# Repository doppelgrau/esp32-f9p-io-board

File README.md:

# ESP32 F9P IO board

This PCB is a versatile IO plattform that provides computing power (ESP32) and IO interfaces to build GPS/RTK applications.

## Hardware Overview

- Power supply: 
    - Input 9V-28V (labeld 12V on the board), external connection on J4. 
    - Protected against wrong polarity (Diode D7 parallel to the relay K1)
    - Reduced inrush current (resistors R15/16 in serie with the starting diode D7 before the relay K1 closes and shortens the path).
    - V78E05-1000 (step down converter) PS1 generates 5V
    - AZ1117-3.3 LDO U2 generates 3V from the 5V supply.
    - 12A (slow) fuse soldered on the board. Recommended to use a 10A external fuse.
- ESP32-WROOM-32 U1 for computing-power, wifi, Bluetooth
- Arduino headers for the simpleRTK2B-F9P (uart 1 of the F9P connected)
- Serial interfaces
    - one uart (IO13/14) on the Arduino headers for the F9P
    - one uart (IO0/2) next to the arduino headers on two pins (J2) for the new simpleRTK2Blight. Since the two pins have a special meaning during boot, pulling TX to GND during startup results in the ESP going into programming mode.
    - one uart (IO15/16) for RS232 on the D-Sub connector J16
    - one uart (IO1/3) on the USB-Uart converter (J14) - Also supports programming with "RTS/DTR"
- I2C (IO32/33)
    - I2C with 3.3V logic level (J8 pin header, J13,17 [qwiic](https://www.sparkfun.com/qwiic) connector)
    - I2C with 5V logic level (J7 pin header)
    - internal used adresses:
        - 0x1C - Magnetometer part of the LSM9DS1 (U12)
        - 0x43 - FXL6408 port extender (IC 1)
        - 0x48 - ADS1115 (U4)
        - 0x6A - Accelerometer part of the LSM9DS1 (U12)
- CAN bus
    - Tranceiver (U2) + ESP32 integrated controler (TX IO5, RX IO35)
    - Termination resistor and sending messages can/must both be enabled with a jumper on J12
    - external connection J18
- Ethernet:
    - internal MAC, connected to LAN8720A on IO17,18,19,21,22,23,25,26,27
        - IO17 Clock
        - IO18 MDIO
        - IO23 MDC
    - PHY-Reset controlled with FXL6408-GPI01
    - ETH-Address of the LAN8720: 0
- IMU: 9 Axis, LSM9DS1 (U12). Magnetometer needs iron correction to be usable.
- Outputs
    - One H-bridge/motordriver with two VNH7070AS (U3/5), (PWM IO4, FXL6408-GPIO6/7 direction). External connected on J4
    - One H-bridge/motordriver with one VNH7070AS (U9), (PWM IO12, FXL6408-GPI04/5 direction), external connected on J3
    - One Relay (K2) controlled on FXL6408-GPI03, external connected on J3
    - One status LED (D2) controlled on FXL6408-GPI02
- Inputs
    - Three 15V tolerant (analog) inputs IO34, SENSOR_VN/36, SENSOR_VP/39, external connected on J1
    - Three 5V tolerant (analog) inputs on the ADS1115, first two cann be used to measure differential. Number four is hardwired to VCC/5V. External connected on J5
    - One Button (e.g. for entering configuration mode), on FXL6408-GPI00
- Connectors:
    - J1 - 6 pin PTSM header. 15V tolerant inputs and 12V for easy cabeling if used as switch
    - J2 - 2 Pin Uart
    - J3 - 7 pin PTSM header. Outputs of second H-bridge, two times ground (for using as two half bridges) and the three pins for the relay (comm, no, nc)
    - J4 - 4 pin CCA header. Power input and output of the first motor driver/h-bridge
    - J5 - 5 pin PTSM header. Three ADS1115 inputs, 5V and GND for easy cabeling (e.g. linear potentiometer)
    - J7 - 4 pin header. I2C 5V logic level + GND and 5V
    - J8 - 4 pin header. I2C 3V3 logic level + GND and 3V3
    - J9, J10, J11 - 8 pin header. Socket for the simpleRTK2B F9P
    - J12 - 2x2 horizontal pin header. Used for jumpers to enable CAN termination and/or CAN TX
    - J13, J17 - qwiic connector. I2C 3V3
    - J14 - micro USB connector. Can power 5V and 3V3 part of the PCB. Electricaly not isolated! Used for programming the ESP32
    - J15 - RJ45 ethernet connector
    - J16 - D-Sub connector (male). RS232
    - J18 - 2 pin PTSM header. CAN bus

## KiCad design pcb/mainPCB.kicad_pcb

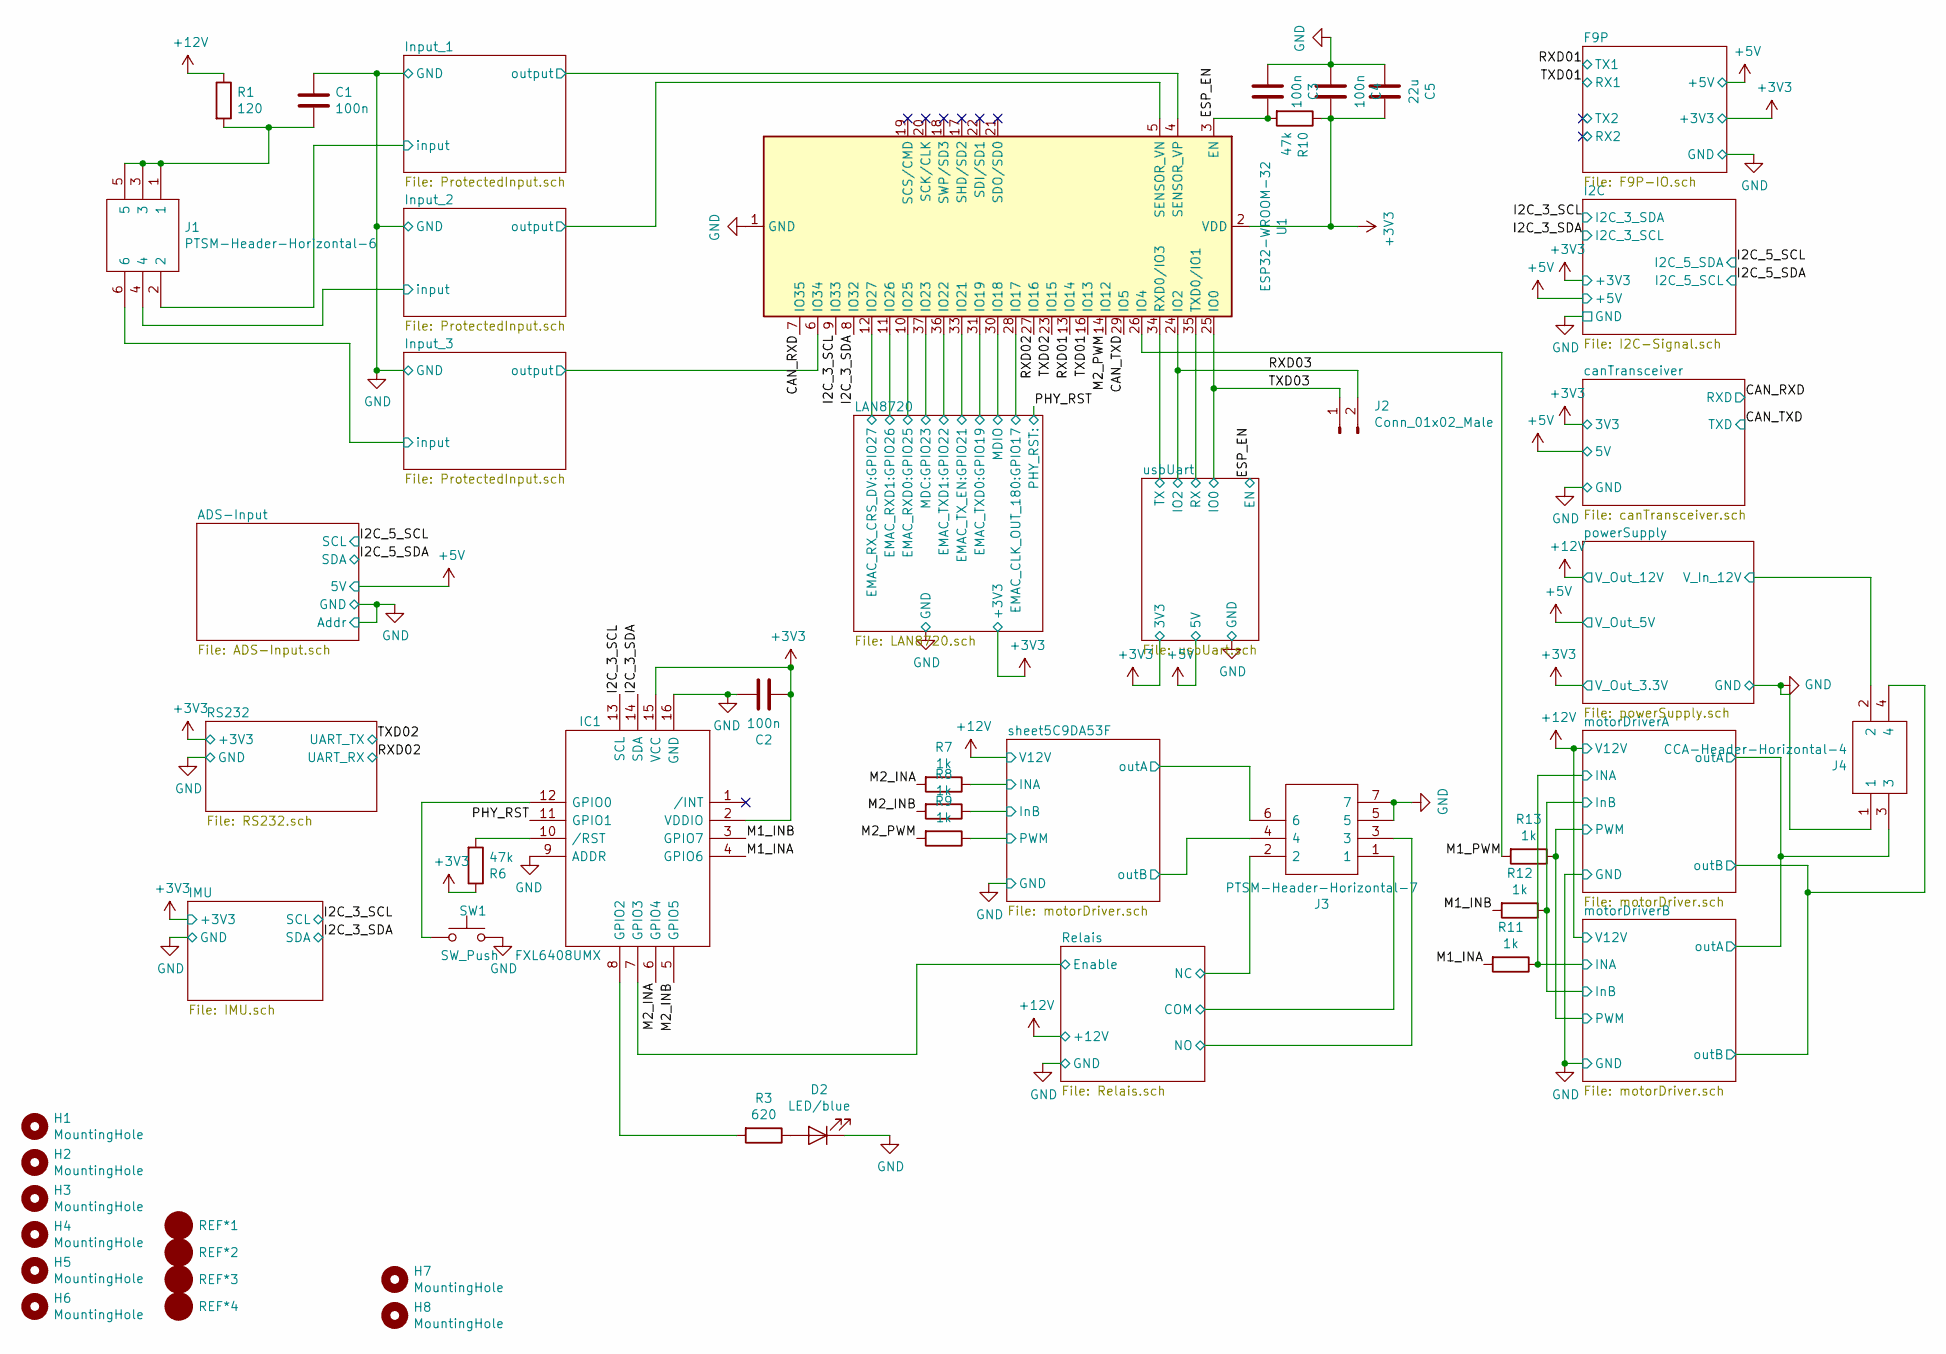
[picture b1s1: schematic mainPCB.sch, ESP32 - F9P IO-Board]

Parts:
C1, C2, C3, C4: 100n; C_0805_2012Metric
C5: 22u; C_0805_2012Metric
D2: LED/blue; C_0805_2012Metric
H1, H2, H3, H4: MountingHole; MountingHole_4.3mm_M4_DIN965
H5, H6, H7, H8: MountingHole; MountingHole_3.2mm_M3_DIN965
IC1: FXL6408UMX; QFN40P180X260X55-16N; Mouser Part Number 512-FXL6408UMX
J1: PTSM-Header-Horizontal-6; 1814883; Mouser Part Number 651-1814883
J2: Conn_01x02_Male; PinHeader_1x02_P2.54mm_Vertical
J3: PTSM-Header-Horizontal-7; 1814896; Mouser Part Number 651-1814896
J4: CCA-Header-Horizontal-4; 1836366; Manufacturer_Part_Number 1836366; Mouser Part Number 651-1836366
R1: 120; R_0805_2012Metric
R3: 620; R_0805_2012Metric
R6, R10: 47k; R_0805_2012Metric
R7, R8, R9, R11, R12, R13: 1k; R_0805_2012Metric
REF*1, REF*2, REF*3, REF*4: Fiducial; Fiducial_1mm_Dia_2mm_Outer
SW1: SW_Push; SW_SPST_PTS645
U1: ESP32-WROOM-32

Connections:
+3V3: C2.1, C4.1, C5.1, IC1.2 (VDDIO), IC1.15 (VCC), R6.1, R10.1, U1.2 (VDD); also elsewhere on the board
+12V: R1.1; also elsewhere on the board
/CAN_RXD: U1.7 (IO35); also elsewhere on the board
/CAN_TXD: U1.29 (IO5); also elsewhere on the board
/ESP_EN: C3.1, R10.2, U1.3 (EN); also elsewhere on the board
/I2C_3_SCL: IC1.13 (SCL), U1.9 (IO33); also elsewhere on the board
/I2C_3_SDA: IC1.14 (SDA), U1.8 (IO32); also elsewhere on the board
/Input_1/input: J1.2; also elsewhere on the board
/Input_1/output: U1.4 (SENSOR_VP); also elsewhere on the board
/Input_2/input: J1.4; also elsewhere on the board
/Input_2/output: U1.5 (SENSOR_VN); also elsewhere on the board
/Input_3/input: J1.6; also elsewhere on the board
/Input_3/output: U1.6 (IO34); also elsewhere on the board
/LAN8720/EMAC_CLK_OUT_180:GPIO17: U1.28 (IO17); also elsewhere on the board
/LAN8720/EMAC_RXD0:GPIO25: U1.10 (IO25); also elsewhere on the board
/LAN8720/EMAC_RXD1:GPIO26: U1.11 (IO26); also elsewhere on the board
/LAN8720/EMAC_RX_CRS_DV:GPIO27: U1.12 (IO27); also elsewhere on the board
/LAN8720/EMAC_TXD0:GPIO19: U1.31 (IO19); also elsewhere on the board
/LAN8720/EMAC_TXD1:GPIO22: U1.36 (IO22); also elsewhere on the board
/LAN8720/EMAC_TX_EN:GPIO21: U1.33 (IO21); also elsewhere on the board
/LAN8720/MDC:GPIO23: U1.37 (IO23); also elsewhere on the board
/LAN8720/MDIO: U1.30 (IO18); also elsewhere on the board
/M1_INA: IC1.4 (GPIO6), R11.2
/M1_INB: IC1.3 (GPIO7), R12.2
/M1_PWM: R13.2, U1.26 (IO4)
/M2_INA: IC1.6 (GPIO4), R7.2
/M2_INB: IC1.5 (GPIO5), R8.2
/M2_PWM: R9.2, U1.14 (IO12)
/PHY_RST: IC1.11 (GPIO1); also elsewhere on the board
/RXD01: U1.13 (IO14); also elsewhere on the board
/RXD02: U1.27 (IO16); also elsewhere on the board
/RXD03: J2.2, U1.24 (IO2); also elsewhere on the board
/Relais/COM: J3.1; also elsewhere on the board
/Relais/Enable: IC1.7 (GPIO3); also elsewhere on the board
/Relais/NC: J3.2; also elsewhere on the board
/Relais/NO: J3.3; also elsewhere on the board
/TXD01: U1.16 (IO13); also elsewhere on the board
/TXD02: U1.23 (IO15); also elsewhere on the board
/TXD03: J2.1, U1.25 (IO0); also elsewhere on the board
/motorDriverA/INA: R11.1; also elsewhere on the board
/motorDriverA/InB: R12.1; also elsewhere on the board
/motorDriverA/PWM: R13.1; also elsewhere on the board
/motorDriverA/outA: J4.3; also elsewhere on the board
/motorDriverA/outB: J4.4; also elsewhere on the board
/powerSupply/V_In_12V: J4.2; also elsewhere on the board
/sheet5C9DA53F/INA: R7.1; also elsewhere on the board
/sheet5C9DA53F/InB: R8.1; also elsewhere on the board
/sheet5C9DA53F/PWM: R9.1; also elsewhere on the board
/sheet5C9DA53F/outA: J3.6; also elsewhere on the board
/sheet5C9DA53F/outB: J3.4; also elsewhere on the board
/usbUart/RX: U1.35 (TXD0/IO1); also elsewhere on the board
/usbUart/TX: U1.34 (RXD0/IO3); also elsewhere on the board
GND: C1.1, C2.2, C3.2, C4.2, C5.2, D2.1 (K), IC1.9 (ADDR), IC1.16 (GND), J3.5, J3.7, J4.1, SW1.2, U1.1 (GND), U1.15 (GND), U1.38 (GND); also elsewhere on the board
unnamed: C1.2, J1.1, J1.3, J1.5, R1.2
unnamed: D2.2 (A), R3.1
unnamed: IC1.8 (GPIO2), R3.2
unnamed: IC1.10 (/RST), R6.2
unnamed: IC1.12 (GPIO0), SW1.1

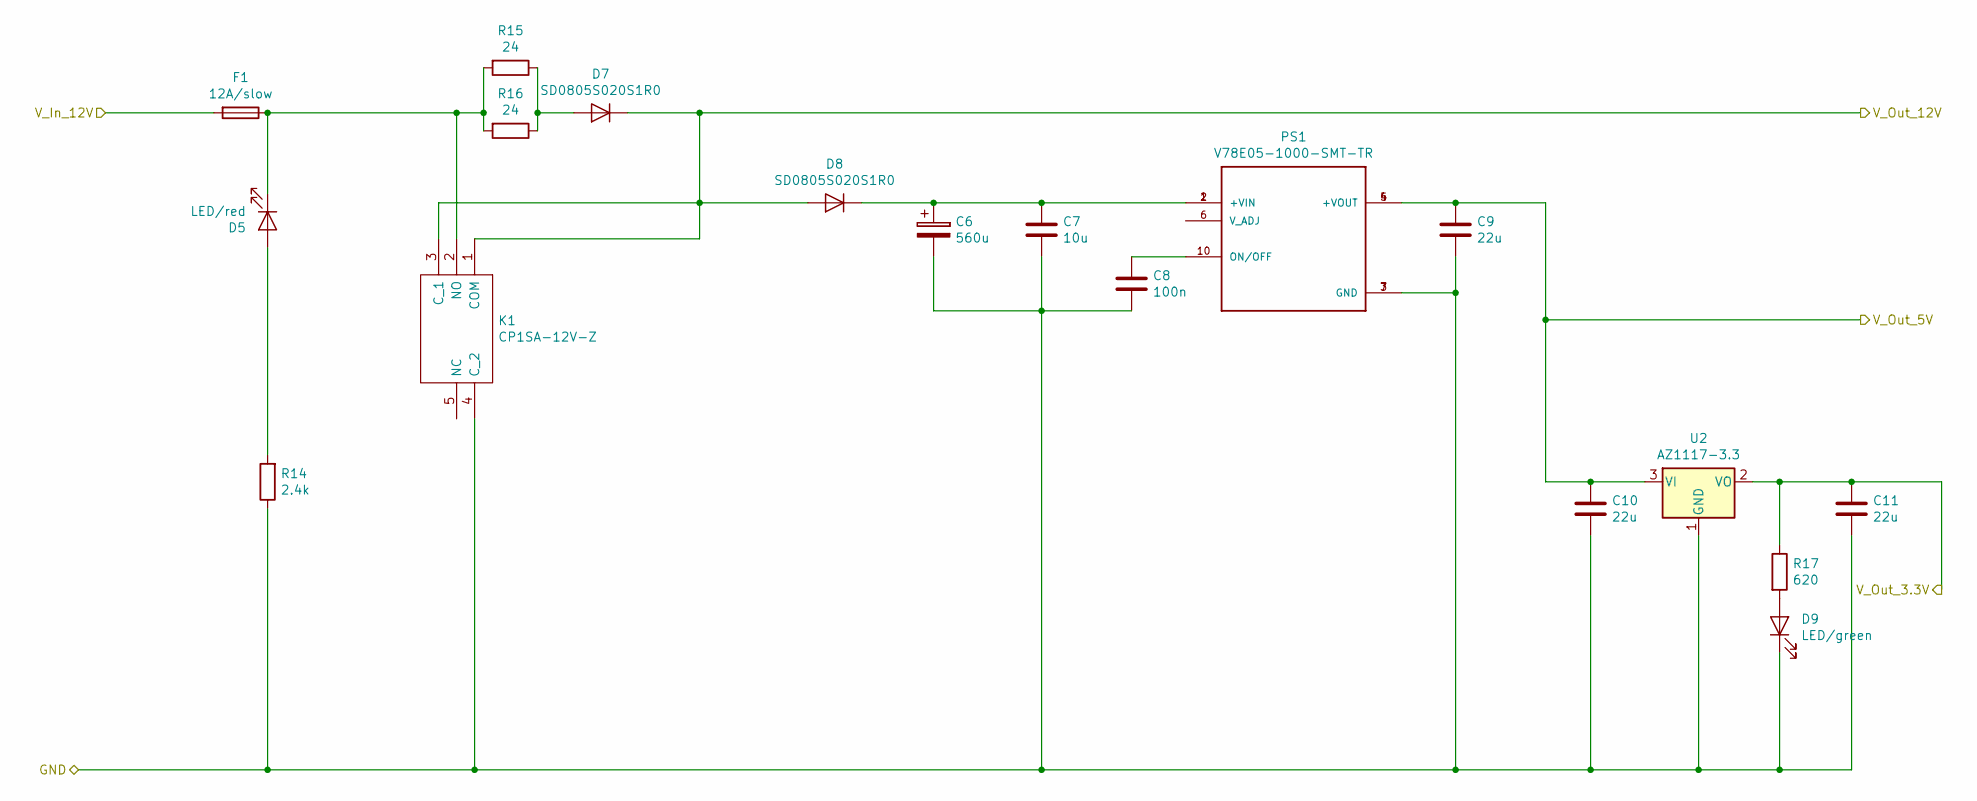
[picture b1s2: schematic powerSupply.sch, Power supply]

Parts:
C6: 560u; CP_Elec_10x10.5
C7: 10u; C_0805_2012Metric
C8: 100n; C_0805_2012Metric
C9, C10, C11: 22u; C_0805_2012Metric
D5: LED/red; C_0805_2012Metric
D7, D8: SD0805S020S1R0; D_0805_2012Metric
D9: LED/green; C_0805_2012Metric
F1: 12A/slow; Fuse_1206_3216Metric
K1: CP1SA-12V-Z; CP1SA12VZ; Mouser Part Number 769-CP1SA-12V-Z
PS1: V78E05-1000-SMT-TR; SOP254P1140X825-10N
R14: 2.4k; R_0805_2012Metric
R15, R16: 24; R_0805_2012Metric
R17: 620; R_0805_2012Metric
U2: AZ1117-3.3; SOT-223-3_TabPin2

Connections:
+3V3: C11.1, R17.1, U2.2 (VO); also elsewhere on the board
+5V: C9.1, C10.1, PS1.4 (+VOUT), PS1.5 (+VOUT), U2.3 (VI); also elsewhere on the board
+12V: D7.1 (K), D8.2 (A), K1.1 (COM), K1.3 (C_1); also elsewhere on the board
/powerSupply/V_In_12V: F1.2; also elsewhere on the board
GND: C6.2, C7.2, C8.2, C9.2, C10.2, C11.2, D9.1 (K), K1.4 (C_2), PS1.3 (GND), PS1.7 (GND), R14.1, U2.1 (GND); also elsewhere on the board
unnamed: C6.1, C7.1, D8.1 (K), PS1.1 (+VIN), PS1.2 (+VIN)
unnamed: C8.1, PS1.10 (ON/OFF)
unnamed: D5.1 (K), F1.1, K1.2 (NO), R15.2, R16.2
unnamed: D5.2 (A), R14.2
unnamed: D7.2 (A), R15.1, R16.1
unnamed: D9.2 (A), R17.2

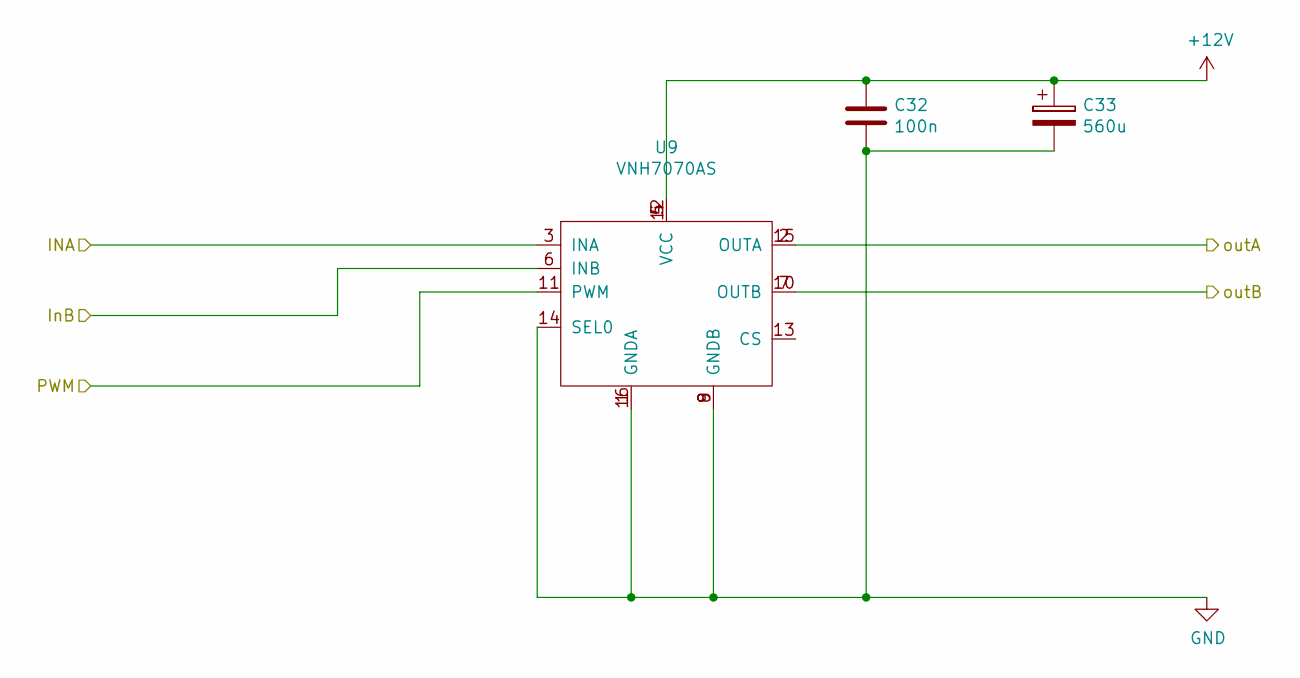
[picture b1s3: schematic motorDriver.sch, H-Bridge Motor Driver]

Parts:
C12: 100n; C_0805_2012Metric
C13: 560u; CP_Elec_10x10.5
U3: VNH7070AS; SOIC-16_3.9x9.9mm_P1.27mm

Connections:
+12V: C12.1, C13.1, U3.4 (VCC), U3.5 (VCC), U3.12 (VCC); also elsewhere on the board
/motorDriverA/INA: U3.3 (INA); also elsewhere on the board
/motorDriverA/InB: U3.6 (INB); also elsewhere on the board
/motorDriverA/PWM: U3.11 (PWM); also elsewhere on the board
/motorDriverA/outA: U3.2 (OUTA), U3.15 (OUTA); also elsewhere on the board
/motorDriverA/outB: U3.7 (OUTB), U3.10 (OUTB); also elsewhere on the board
GND: C12.2, C13.2, U3.1 (GNDA), U3.8 (GNDB), U3.9 (GNDB), U3.14 (SEL0), U3.16 (GNDA); also elsewhere on the board

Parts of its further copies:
C21, C32: 100n; C_0805_2012Metric
C22, C33: 560u; CP_Elec_10x10.5
U5, U9: VNH7070AS; SOIC-16_3.9x9.9mm_P1.27mm

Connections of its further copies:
+12V: C21.1, C22.1, C32.1, C33.1, U5.4 (VCC), U5.5 (VCC), U5.12 (VCC), U9.4 (VCC), U9.5 (VCC), U9.12 (VCC); also elsewhere on the board
/motorDriverA/INA: U5.3 (INA); also elsewhere on the board
/motorDriverA/InB: U5.6 (INB); also elsewhere on the board
/motorDriverA/PWM: U5.11 (PWM); also elsewhere on the board
/motorDriverA/outA: U5.2 (OUTA), U5.15 (OUTA); also elsewhere on the board
/motorDriverA/outB: U5.7 (OUTB), U5.10 (OUTB); also elsewhere on the board
/sheet5C9DA53F/INA: U9.3 (INA); also elsewhere on the board
/sheet5C9DA53F/InB: U9.6 (INB); also elsewhere on the board
/sheet5C9DA53F/PWM: U9.11 (PWM); also elsewhere on the board
/sheet5C9DA53F/outA: U9.2 (OUTA), U9.15 (OUTA); also elsewhere on the board
/sheet5C9DA53F/outB: U9.7 (OUTB), U9.10 (OUTB); also elsewhere on the board
GND: C21.2, C22.2, C32.2, C33.2, U5.1 (GNDA), U5.8 (GNDB), U5.9 (GNDB), U5.14 (SEL0), U5.16 (GNDA), U9.1 (GNDA), U9.8 (GNDB), U9.9 (GNDB), U9.14 (SEL0), U9.16 (GNDA); also elsewhere on the board

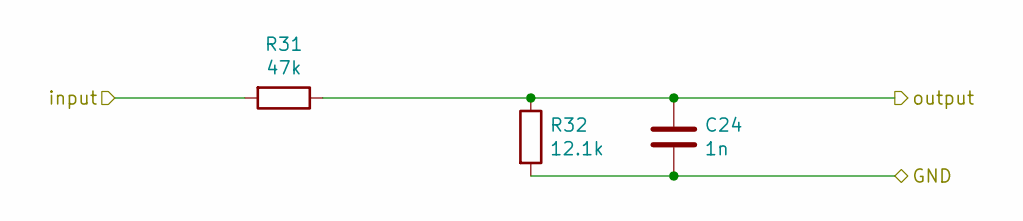
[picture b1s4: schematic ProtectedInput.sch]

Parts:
C14: 1n; C_0805_2012Metric
R18: 47k; R_0805_2012Metric
R19: 12.1k; R_0805_2012Metric

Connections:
/Input_1/input: R18.2; also elsewhere on the board
/Input_1/output: C14.1, R18.1, R19.1; also elsewhere on the board
GND: C14.2, R19.2; also elsewhere on the board

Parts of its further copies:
C15, C24: 1n; C_0805_2012Metric
R20, R31: 47k; R_0805_2012Metric
R21, R32: 12.1k; R_0805_2012Metric

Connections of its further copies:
/Input_2/input: R20.2; also elsewhere on the board
/Input_2/output: C15.1, R20.1, R21.1; also elsewhere on the board
/Input_3/input: R31.2; also elsewhere on the board
/Input_3/output: C24.1, R31.1, R32.1; also elsewhere on the board
GND: C15.2, C24.2, R21.2, R32.2; also elsewhere on the board

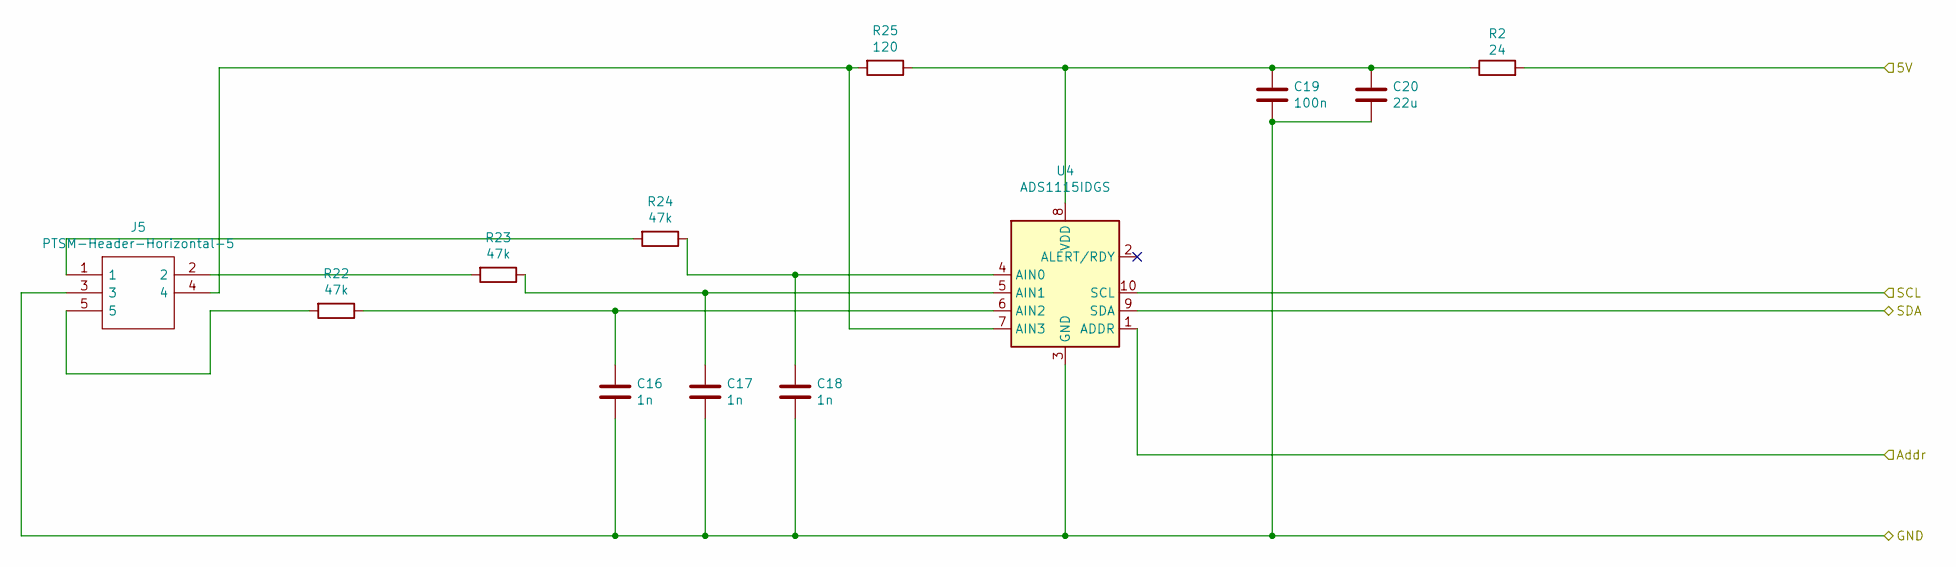
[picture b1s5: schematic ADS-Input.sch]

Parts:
C16, C17, C18: 1n; C_0805_2012Metric
C19: 100n; C_0805_2012Metric
C20: 22u; C_0805_2012Metric
J5: PTSM-Header-Horizontal-5; 1814870; Mouser Part Number 651-1814870
R2: 24; R_0805_2012Metric
R22, R23, R24: 47k; R_0805_2012Metric
R25: 120; R_0805_2012Metric
U4: ADS1115IDGS; MSOP-10_3x3mm_P0.5mm

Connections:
+5V: R2.2; also elsewhere on the board
/I2C_5_SCL: U4.10 (SCL); also elsewhere on the board
/I2C_5_SDA: U4.9 (SDA); also elsewhere on the board
GND: C16.2, C17.2, C18.2, C19.2, C20.2, J5.3, U4.1 (ADDR), U4.3 (GND); also elsewhere on the board
unnamed: C16.1, R22.1, U4.6 (AIN2)
unnamed: C17.1, R23.1, U4.5 (AIN1)
unnamed: C18.1, R24.1, U4.4 (AIN0)
unnamed: C19.1, C20.1, R2.1, R25.1, U4.8 (VDD)
unnamed: J5.1, R24.2
unnamed: J5.2, R23.2
unnamed: J5.4, R25.2, U4.7 (AIN3)
unnamed: J5.5, R22.2

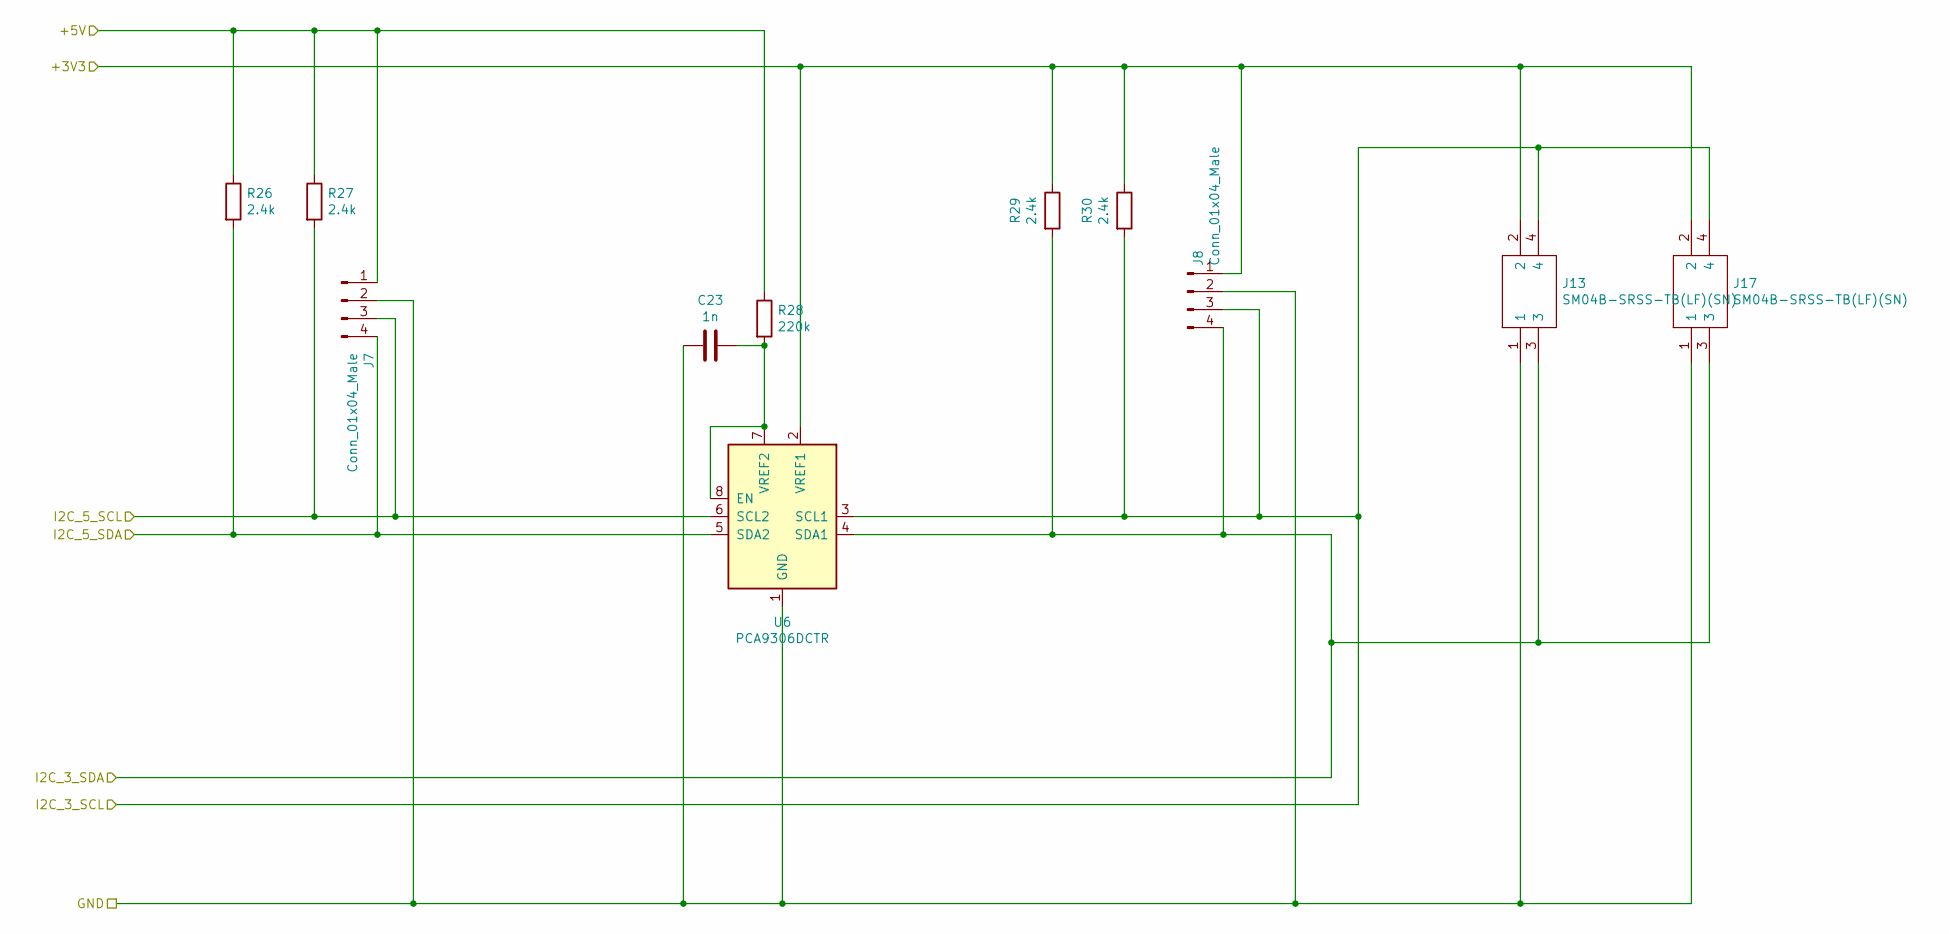
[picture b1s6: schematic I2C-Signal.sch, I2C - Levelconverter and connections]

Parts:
C23: 1n; C_0805_2012Metric
J7: Conn_01x04_Male; PinHeader_1x04_P2.54mm_Horizontal
J8: Conn_01x04_Male; PinHeader_1x04_P2.54mm_Vertical
J13, J17: SM04B-SRSS-TB(LF)(SN); JST_SH_SM04B-SRSS-TB_1x04-1MP_P1.00mm_Horizontal; Manufacturer_Part_Number SM04B-SRSS-TB(LF)(SN)
R26, R27, R29, R30: 2.4k; R_0805_2012Metric
R28: 220k; R_0805_2012Metric
U6: PCA9306DCTR; SSOP-8_2.95x2.8mm_P0.65mm

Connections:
+3V3: J8.1, J13.2, J17.2, R29.1, R30.1, U6.2 (VREF1); also elsewhere on the board
+5V: J7.1, R26.1, R27.1, R28.1; also elsewhere on the board
/I2C_3_SCL: J8.4, J13.3, J17.3, R29.2, U6.4 (SDA1); also elsewhere on the board
/I2C_3_SDA: J8.3, J13.4, J17.4, R30.2, U6.3 (SCL1); also elsewhere on the board
/I2C_5_SCL: J7.4, R26.2, U6.5 (SDA2); also elsewhere on the board
/I2C_5_SDA: J7.3, R27.2, U6.6 (SCL2); also elsewhere on the board
GND: C23.2, J7.2, J8.2, J13.1, J17.1, U6.1 (GND); also elsewhere on the board
unnamed: C23.1, R28.2, U6.7 (VREF2), U6.8 (EN)

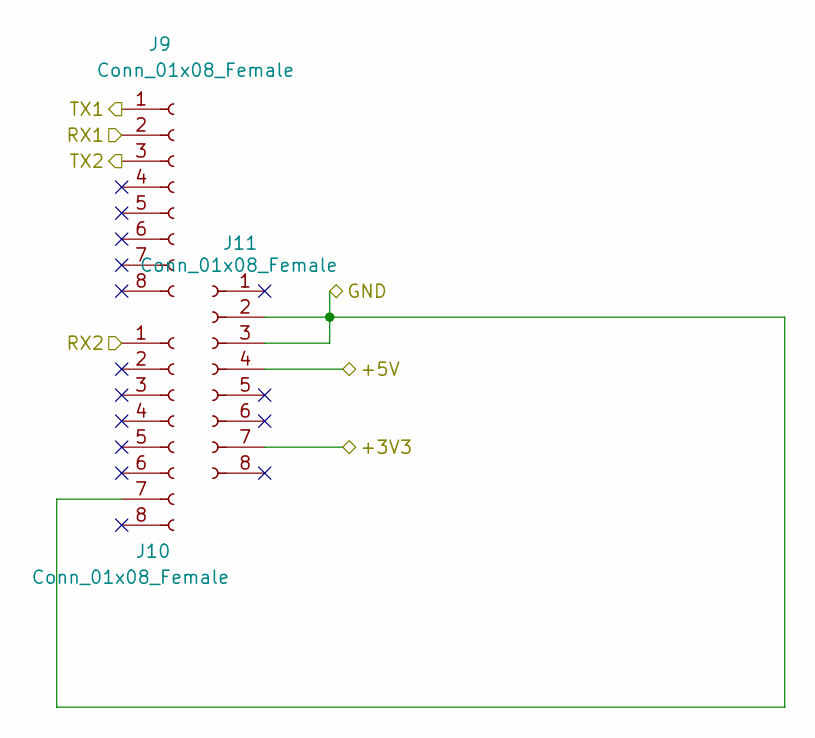
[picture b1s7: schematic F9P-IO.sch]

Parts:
J9, J10, J11: Conn_01x08_Female; PinSocket_1x08_P2.54mm_Vertical

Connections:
+3V3: J11.7; also elsewhere on the board
+5V: J11.4; also elsewhere on the board
/F9P/RX2: J10.1
/F9P/TX2: J9.3
/RXD01: J9.1; also elsewhere on the board
/TXD01: J9.2; also elsewhere on the board
GND: J10.7, J11.2, J11.3; also elsewhere on the board

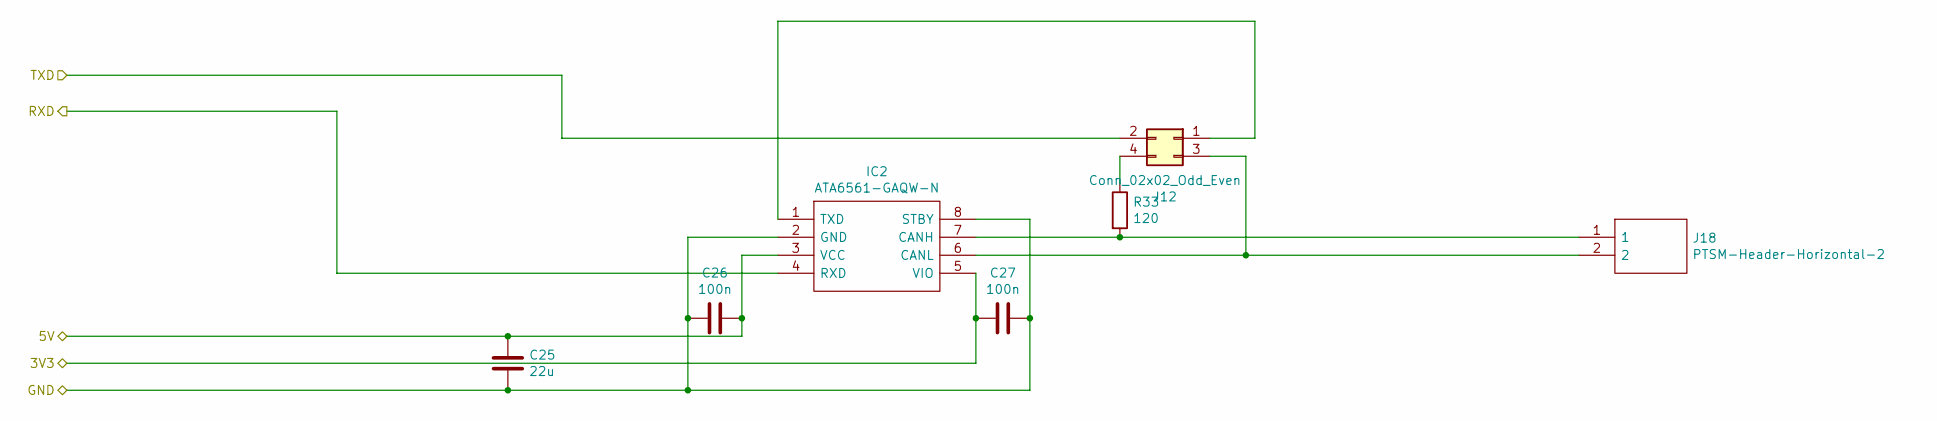
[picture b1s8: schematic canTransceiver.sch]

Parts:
C25: 22u; C_0805_2012Metric
C26, C27: 100n; C_0805_2012Metric
IC2: ATA6561-GAQW-N; SOIC127P600X175-8N; Mouser Part Number 579-ATA6561-GAQW-N
J12: Conn_02x02_Odd_Even; PinHeader_2x02_P2.54mm_Horizontal
J18: PTSM-Header-Horizontal-2; 1814841; Mouser Part Number 651-1814841
R33: 120; R_0805_2012Metric

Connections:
+3V3: C27.2, IC2.5 (VIO); also elsewhere on the board
+5V: C25.1, C26.1, IC2.3 (VCC); also elsewhere on the board
/CAN_RXD: IC2.4 (RXD); also elsewhere on the board
/CAN_TXD: J12.2; also elsewhere on the board
GND: C25.2, C26.2, C27.1, IC2.2 (GND), IC2.8 (STBY); also elsewhere on the board
unnamed: IC2.1 (TXD), J12.1
unnamed: IC2.6 (CANL), J12.3, J18.2
unnamed: IC2.7 (CANH), J18.1, R33.2
unnamed: J12.4, R33.1

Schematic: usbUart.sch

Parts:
C28, C29, C30: 100n; C_0805_2012Metric
C31: 2.2u; C_0805_2012Metric
D10: BAT54C; SOT-23
D11: SD0805S020S1R0; D_0805_2012Metric
J14: USB_B_Micro; USB_Micro-B_Molex-105017-0001
Q1, Q2: BC817-40,215; SOT95P230X110-3N; Mouser Part Number 771-BC817-40-T/R
R34: 22.1k; R_0805_2012Metric
R35: 47k; R_0805_2012Metric
R36, R37, R40: 1k; R_0805_2012Metric
R38, R39, R41: 120; R_0805_2012Metric
U7: TPD3E001DRLR; SOT-553
U8: CP2102N-A01-GQFN24; QFN-24-1EP_4x4mm_P0.5mm_EP2.6x2.6mm

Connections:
+3V3: C29.2, C30.2, C31.2, R36.1, U8.5 (VIO), U8.6 (VDD), U8.7 (REGIN); also elsewhere on the board
+5V: D11.1 (K); also elsewhere on the board
/ESP_EN: Q2.3; also elsewhere on the board
/RXD03: D10.2; also elsewhere on the board
/TXD03: D10.1; also elsewhere on the board
/usbUart/RX: R39.1; also elsewhere on the board
/usbUart/TX: R38.1; also elsewhere on the board
GND: C28.2, C29.1, C30.1, C31.1, J14.5 (GND), J14.6 (Shield), R35.1, U7.3, U8.2 (GND), U8.25 (GND); also elsewhere on the board
unnamed: C28.1, D11.2 (A), J14.1 (VBUS), R34.2, U7.5
unnamed: D10.3, R41.1
unnamed: J14.2 (D-), U7.4 (IO3), U8.4 (D-)
unnamed: J14.3 (D+), U7.2 (IO2), U8.3 (D+)
unnamed: J14.4 (ID), U7.1 (IO1)
unnamed: Q1.1, R37.1
unnamed: Q1.2, R40.2, U8.23 (DTR)
unnamed: Q1.3, R41.2
unnamed: Q2.1, R40.1
unnamed: Q2.2, R37.2, U8.19 (RTS)
unnamed: R34.1, R35.2, U8.8 (VBUS)
unnamed: R36.2, U8.9 (~RSTb)
unnamed: R38.2, U8.21 (TXD)
unnamed: R39.2, U8.20 (RXD)

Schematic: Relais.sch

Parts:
K2: CP1SA-12V-Z; CP1SA12VZ; Mouser Part Number 769-CP1SA-12V-Z
U10: NUD3124LT1G; SOT95P237X100-3N; Manufacturer_Part_Number NUD3124LT1G

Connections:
+12V: K2.3 (C_1); also elsewhere on the board
/Relais/COM: K2.1 (COM); also elsewhere on the board
/Relais/Enable: U10.1 (GATE); also elsewhere on the board
/Relais/NC: K2.5 (NC); also elsewhere on the board
/Relais/NO: K2.2 (NO); also elsewhere on the board
GND: U10.2 (SOURCE); also elsewhere on the board
unnamed: K2.4 (C_2), U10.3 (DRAIN)

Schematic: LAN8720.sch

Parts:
C34: 1n/2000V; C_1206_3216Metric
C35: 100n/16V; C_0805_2012Metric
C36, C38, C39, C41: 100n; C_0805_2012Metric
C37: 22u; C_0805_2012Metric
C40: 2.2u; C_0805_2012Metric
FB1: 600R/2A; L_0805_2012Metric
J15: RJ45_Amphenol_RJMG1BD3B8K1ANR
R42, R44: 0; R_0805_2012Metric
R43, R50, R51, R52, R53: 2.4k; R_0805_2012Metric
R45, R46, R47, R49: 49.9; R_0805_2012Metric
R48: 12.1k; R_0805_2012Metric
U11: LAN8720A; QFN-24-1EP_4x4mm_P0.5mm_EP2.6x2.6mm

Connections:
+3V3: C41.2, FB1.1, U11.9 (VDDIO); also elsewhere on the board
/LAN8720/+3V3LAN: C36.1, C37.1, C38.1, FB1.2, R44.2, R45.2, R46.2, R47.2, R49.2, R50.2, R51.2, R52.2, R53.2, U11.1 (VDD2A), U11.19 (VDD1A)
/LAN8720/EMAC_CLK_OUT_180:GPIO17: U11.5 (XTAL1/CLKIN); also elsewhere on the board
/LAN8720/EMAC_RXD0:GPIO25: R51.1, U11.8 (RXD0/MODE0); also elsewhere on the board
/LAN8720/EMAC_RXD1:GPIO26: R52.1, U11.7 (RXD1/MODE1); also elsewhere on the board
/LAN8720/EMAC_RX_CRS_DV:GPIO27: R53.1, U11.11 (CRS_DV/MODE2); also elsewhere on the board
/LAN8720/EMAC_TXD0:GPIO19: U11.17 (TXD0); also elsewhere on the board
/LAN8720/EMAC_TXD1:GPIO22: U11.18 (TXD1); also elsewhere on the board
/LAN8720/EMAC_TX_EN:GPIO21: U11.16 (TXEN); also elsewhere on the board
/LAN8720/MDC:GPIO23: U11.13 (MDC); also elsewhere on the board
/LAN8720/MDIO: U11.12 (MDIO); also elsewhere on the board
/LAN8720/RD+: J15.R3 (RD+), R46.1, U11.23 (RXP)
/LAN8720/RD-: J15.R6 (RD-), R49.1, U11.22 (RXN)
/LAN8720/TD-: J15.R2 (TD-), R47.1, U11.20 (TXN)
/PHY_RST: U11.15 (RST); also elsewhere on the board
GND: C35.1, C36.2, C37.2, C38.2, C39.1, C40.1, C41.1, R42.1, R43.2, R48.1, U11.10 (RXER/PHYAD0), U11.25 (VSS); also elsewhere on the board
unnamed: C34.1, J15.R8 (GND), R42.2
unnamed: C34.2, J15.13 (SHIELD)
unnamed: C35.2, J15.R4 (TCT), J15.R5 (RCT), R44.1
unnamed: C39.2, C40.2, U11.6 (VDDCR)
unnamed: J15.L1 (LEDY_A), U11.3 (LED1/REGOFF)
unnamed: J15.L2 (LEDY_K), R43.1
unnamed: J15.L3 (LEDG_K), U11.2 (LED2/nINTSEL)
unnamed: J15.L4 (LEDG_A), R50.1
unnamed: J15.R1 (TD+), R45.1, U11.21 (TXP)
unnamed: R48.2, U11.24 (RBIAS)

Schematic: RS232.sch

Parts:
C42, C43, C44, C45, C46: 100n; C_0805_2012Metric
IC3: ICL3221EIVZ; SOP65P640X120-16N; Manufacturer_Part_Number ICL3221EIVZ
J16: DB9_Male_MountingHoles; LD09P33E4GV00LF

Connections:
+3V3: C46.1, IC3.12 (FORCEON), IC3.15 (VCC), IC3.16 (FORCEOFF); also elsewhere on the board
/RXD02: IC3.9 (R1OUT); also elsewhere on the board
/TXD02: IC3.11 (T1IN); also elsewhere on the board
GND: C42.2, C45.2, C46.2, IC3.1 (EN), IC3.14 (GND), J16.0 (PAD), J16.5; also elsewhere on the board
unnamed: C42.1, IC3.7 (V-)
unnamed: C43.1, IC3.6 (C2-)
unnamed: C43.2, IC3.5 (C2+)
unnamed: C44.1, IC3.4 (C1-)
unnamed: C44.2, IC3.2 (C1+)
unnamed: C45.1, IC3.3 (V+)
unnamed: IC3.8 (R1IN), J16.2
unnamed: IC3.13 (T1OUT), J16.3

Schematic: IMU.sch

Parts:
C47: 10n; C_0805_2012Metric
C48, C49, C51: 100n; C_0805_2012Metric
C50: 10u; C_0805_2012Metric
R54: 24; R_0805_2012Metric
U12: LSM9DS1; LGA-24L_3x3.5mm_P0.43mm

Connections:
+3V3: C49.2, R54.1, U12.1 (VDDIO), U12.3 (VDDIO), U12.7 (CS_A/G), U12.8 (CS_M); also elsewhere on the board
/I2C_3_SCL: U12.2 (SCL/SPC); also elsewhere on the board
/I2C_3_SDA: U12.4 (SDA/SDI/SDO); also elsewhere on the board
GND: C47.1, C48.1, C49.1, C50.1, C51.1, U12.5 (SDO_A/G), U12.6 (SDO_M), U12.14 (RES), U12.15 (RES), U12.16 (RES), U12.17 (RES), U12.18 (RES), U12.19 (GND), U12.20 (GND); also elsewhere on the board
unnamed: C47.2, U12.21 (CAP)
unnamed: C48.2, U12.24 (C1)
unnamed: C50.2, C51.2, R54.2, U12.22 (VDD), U12.23 (VDD)
